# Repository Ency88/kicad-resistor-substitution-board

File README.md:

# KiCad - Resistor Substitution Board

This repo contains all necessary files to get and change Resistor Substitution Board in KiCad.

Project contains schematic & pcb design

### Schematic

### 3D View

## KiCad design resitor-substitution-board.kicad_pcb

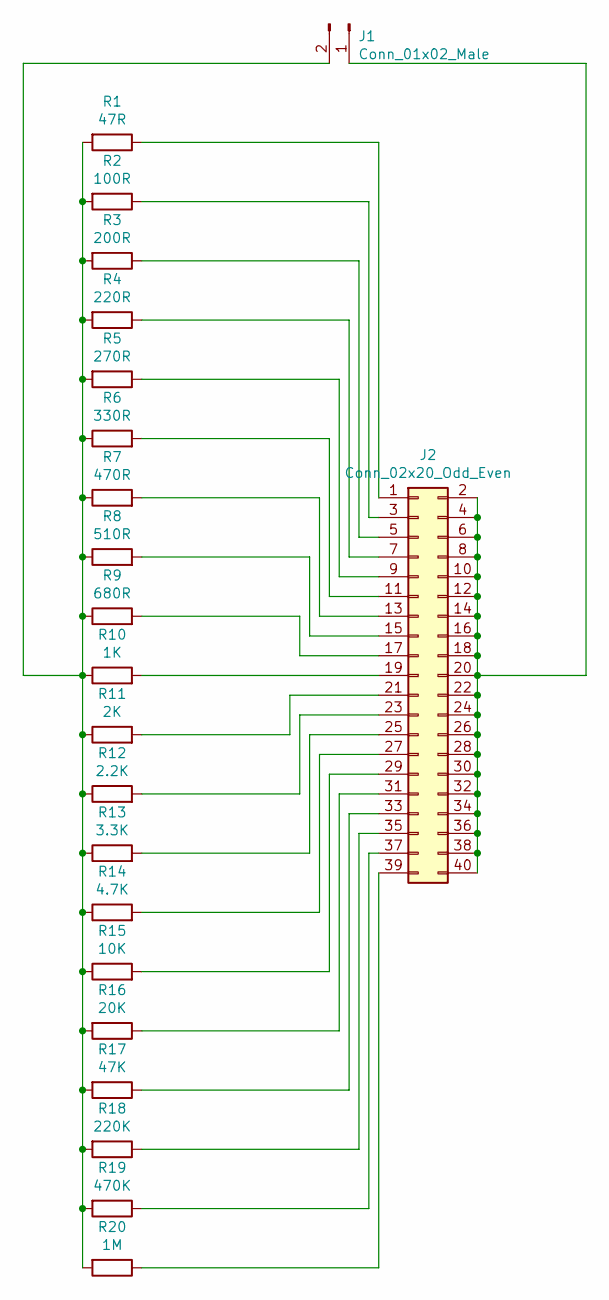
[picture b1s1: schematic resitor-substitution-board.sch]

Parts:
J1: Conn_01x02_Male; PinHeader_1x02_P2.54mm_Vertical
J2: Conn_02x20_Odd_Even; PinHeader_2x20_P2.54mm_Vertical
R1: 47R; R_Axial_DIN0207_L6.3mm_D2.5mm_P7.62mm_Horizontal
R2: 100R; R_Axial_DIN0207_L6.3mm_D2.5mm_P7.62mm_Horizontal
R3: 200R; R_Axial_DIN0207_L6.3mm_D2.5mm_P7.62mm_Horizontal
R4: 220R; R_Axial_DIN0207_L6.3mm_D2.5mm_P7.62mm_Horizontal
R5: 270R; R_Axial_DIN0207_L6.3mm_D2.5mm_P7.62mm_Horizontal
R6: 330R; R_Axial_DIN0207_L6.3mm_D2.5mm_P7.62mm_Horizontal
R7: 470R; R_Axial_DIN0207_L6.3mm_D2.5mm_P7.62mm_Horizontal
R8: 510R; R_Axial_DIN0207_L6.3mm_D2.5mm_P7.62mm_Horizontal
R9: 680R; R_Axial_DIN0207_L6.3mm_D2.5mm_P7.62mm_Horizontal
R10: 1K; R_Axial_DIN0207_L6.3mm_D2.5mm_P7.62mm_Horizontal
R11: 2K; R_Axial_DIN0207_L6.3mm_D2.5mm_P7.62mm_Horizontal
R12: 2.2K; R_Axial_DIN0207_L6.3mm_D2.5mm_P7.62mm_Horizontal
R13: 3.3K; R_Axial_DIN0207_L6.3mm_D2.5mm_P7.62mm_Horizontal
R14: 4.7K; R_Axial_DIN0207_L6.3mm_D2.5mm_P7.62mm_Horizontal
R15: 10K; R_Axial_DIN0207_L6.3mm_D2.5mm_P7.62mm_Horizontal
R16: 20K; R_Axial_DIN0207_L6.3mm_D2.5mm_P7.62mm_Horizontal
R17: 47K; R_Axial_DIN0207_L6.3mm_D2.5mm_P7.62mm_Horizontal
R18: 220K; R_Axial_DIN0207_L6.3mm_D2.5mm_P7.62mm_Horizontal
R19: 470K; R_Axial_DIN0207_L6.3mm_D2.5mm_P7.62mm_Horizontal
R20: 1M; R_Axial_DIN0207_L6.3mm_D2.5mm_P7.62mm_Horizontal

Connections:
unnamed: J1.1, J2.2, J2.4, J2.6, J2.8, J2.10, J2.12, J2.14, J2.16, J2.18, J2.20, J2.22, J2.24, J2.26, J2.28, J2.30, J2.32, J2.34, J2.36, J2.38, J2.40
unnamed: J1.2, R1.2, R2.2, R3.2, R4.2, R5.2, R6.1, R7.1, R8.1, R9.1, R10.1, R11.1, R12.1, R13.1, R14.1, R15.1, R16.2, R17.2, R18.2, R19.2, R20.2
unnamed: J2.1, R1.1
unnamed: J2.3, R2.1
unnamed: J2.5, R3.1
unnamed: J2.7, R4.1
unnamed: J2.9, R5.1
unnamed: J2.11, R6.2
unnamed: J2.13, R7.2
unnamed: J2.15, R8.2
unnamed: J2.17, R9.2
unnamed: J2.19, R10.2
unnamed: J2.21, R11.2
unnamed: J2.23, R12.2
unnamed: J2.25, R13.2
unnamed: J2.27, R14.2
unnamed: J2.29, R15.2
unnamed: J2.31, R16.1
unnamed: J2.33, R17.1
unnamed: J2.35, R18.1
unnamed: J2.37, R19.1
unnamed: J2.39, R20.1

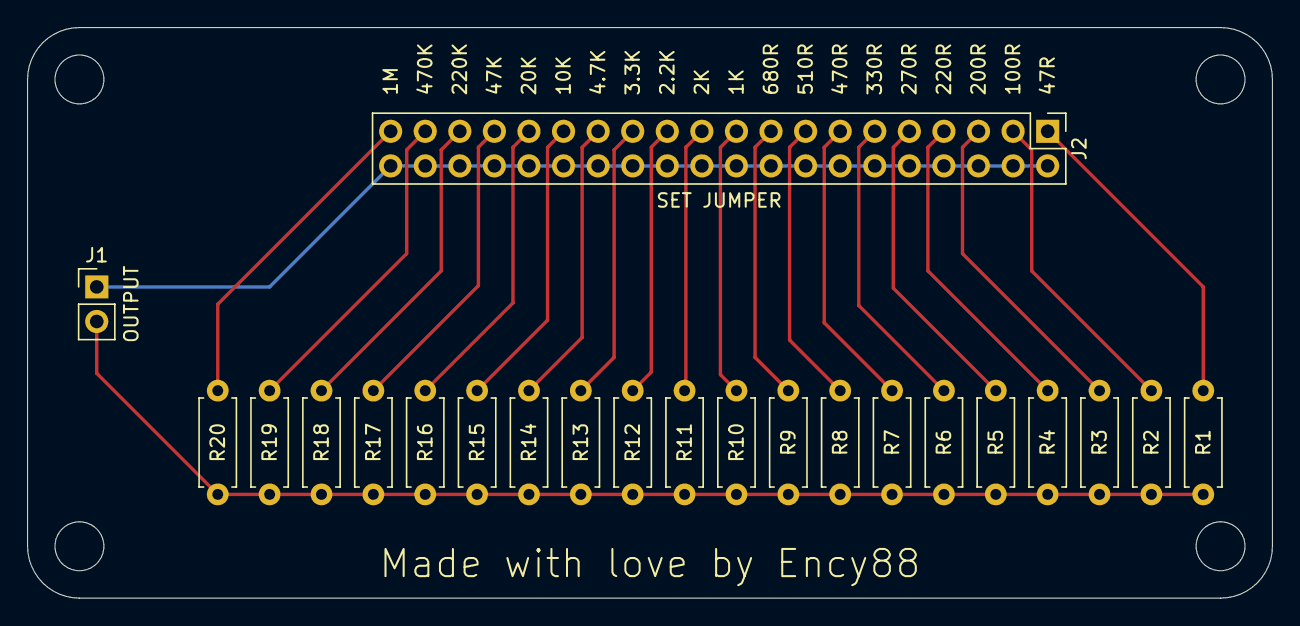
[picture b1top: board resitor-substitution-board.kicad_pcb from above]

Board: 2 copper layers, 91.4 x 41.9 mm, 22 parts (0 on the bottom side), 22 nets.

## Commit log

2021-04-04 Created resistor substitution board
2021-04-04 readme and pictures was added
